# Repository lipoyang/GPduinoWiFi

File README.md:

GPduino WiFi
=========

## 概要
GPduino WiFiは、ESP8266搭載のWiFiラジコン制御ボードです。  
GPduinoに関する詳細は、[GPduinoサポートページ](http://lipoyang.net/gpduino)をごらんください。  
GPduinoWiFiの回路/基板設計データとプリセットファームウェアのソースをここに公開します。

## ファイル一覧

* firm/GPduinoWiFi/ : ファームウェア(ESP8266のArduinoスケッチ)
* hard/GPduinoWiFi/
	* GPduinoWiFi.sch/brd: 回路/基板設計データ(Eagle形式)
	* GPduinoWiFi.pdf: 回路図(PDF)
	* GPduinoWiFi_BOM.xlsx: BOMリスト(Excel形式)
	* GPduinoWiFi.GBL/GBO/GBP/GBS/GML/GTL/GTO/GTP/GTS/TXT: ガーバデータ
* LICENSE: Apache Licence 2.0です。
	* ただし、回路/基板設計は、Creative Commons Attribution Share-Alike 3.0です。
* README.md これ

## ファームウェアの書き込み
GPduino WiFi はESP8266を搭載しており、Arduinoでファームウェアを開発できます。

* 書き込みには、USBシリアル変換基板が必要です。CN11に接続してください。
	* SparkFun製 FTDI Basic Breakout - 3.3V を推奨します。かならず、3.3Vのものを使用してください。
* まず、ArduinoIDE をインストールしておきます。 (ここでは 1.6.9 を使用)
* [ファイル] > [環境設定] > [Additional Boards Manager URLs:]に下記URLをコピペ
	* http://arduino.esp8266.com/stable/package_esp8266com_index.json (安定版)
	* http://arduino.esp8266.com/staging/package_esp8266com_index.json (開発版)
* [ツール] > [ボード] > [ボードマネージャ] で [esp8266] をインストール
* [ツール] > [ボード] で [Generic ESP8266 Module]を選択
	* Flash Mode : QIO
	* Flash Frequency : 40MHz
	* Upload Using : Serial
	* CPU Frequency : 80MHz
	* Flash Size : 4M(3M SPIFFS)　(3MBをファイルシステムで使用 / 1MBをスケッチで使用)
	* Debug port : Disabled
	* Debug Level : None
	* Reset Method : nodemcu
	* Upload Speed : 115200
	* シリアルポート : USBシリアルのCOM番号
	* 書込装置 : USBasp
* BOOTボタン(SW3)を押し下げた状態で、RESETボタン(SW2)を押して離します。
* Uploadボタンで、ファームウェアを書き込みます。

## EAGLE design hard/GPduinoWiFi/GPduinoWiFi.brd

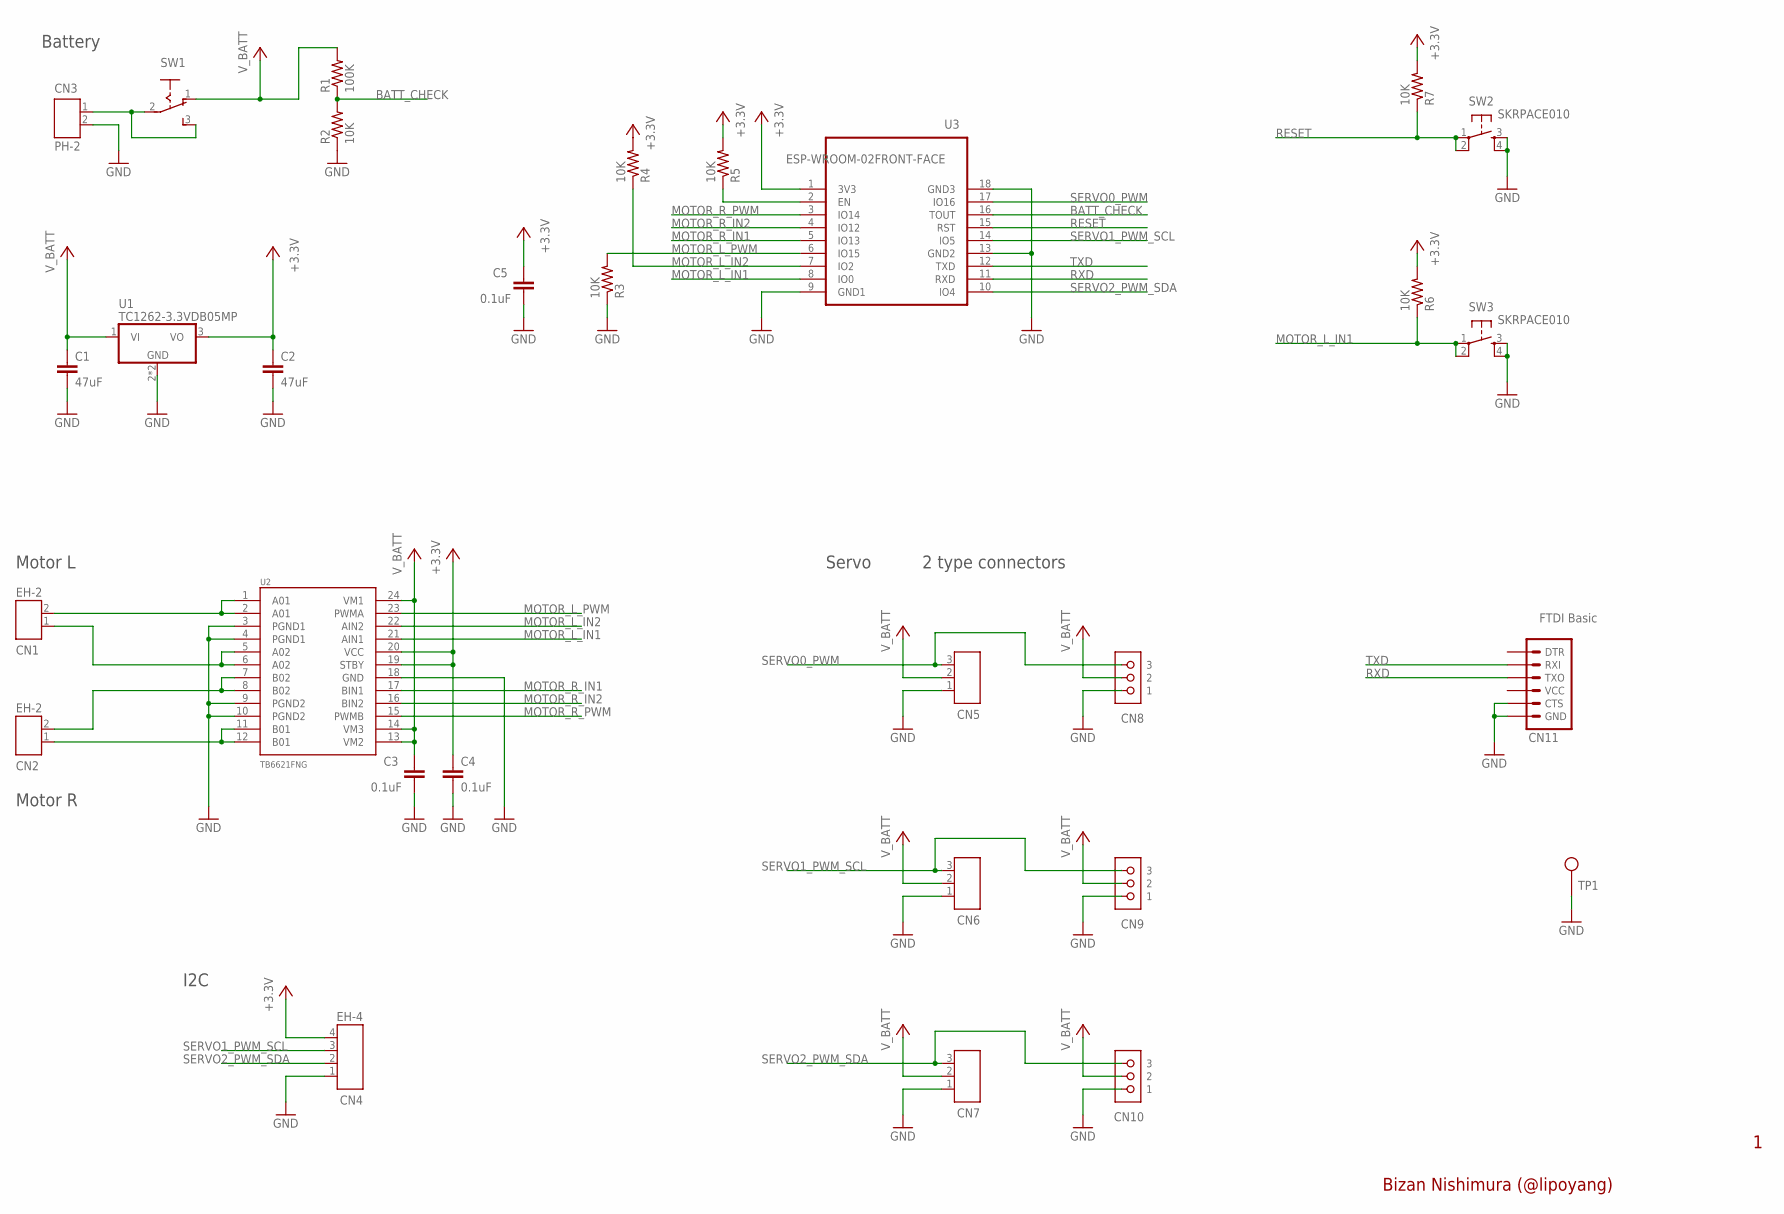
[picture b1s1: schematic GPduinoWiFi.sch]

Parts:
C1, C2: 47uF; C3216
C3, C4, C5: 0.1uF; C1608
CN1, CN2: EH-2
CN3: PH-2
CN4: EH-4
CN5, CN6, CN7: PICOBLADE-3
CN8, CN9, CN10: cn6; CON_RC_SERVO
CN11: FTDI Basic; 1X06
R1: 100K; 0603-RES
R2, R3, R4, R5, R6, R7: 10K; 0603-RES
SW1: SW1; SLIDE-SW
SW2, SW3: SKRPACE010
TP1: TEST_PIN
U1: TC1262-3.3VDB05MP; SOT223
U2: TB6621FNG; SSOP24
U3: ESP-WROOM-02FRONT-FACE; FRONT-FACE

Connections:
+3V3: C2.1, C4.1, C5.1, CN4.4, R4.2, R5.2, R6.2, R7.2, U1.3 (VO), U2.19 (STBY), U2.20 (VCC), U3.1 (3V3)
A01: CN1.2, U2.1 (A01), U2.2 (A01)
A02: CN1.1, U2.5 (A02), U2.6 (A02)
BATT_CHECK: R1.1, R2.2, U3.16 (TOUT)
GND: C1.2, C2.2, C3.2, C4.2, C5.2, CN3.2, CN4.1, CN5.1, CN6.1, CN7.1, CN8.1, CN9.1, CN10.1, CN11.5 (CTS), CN11.6 (GND), R2.1, R3.1, SW2.3, SW2.4, SW3.3, SW3.4, TP1.1, U1.2 (GND), U1.4 (GND), U2.3 (PGND1), U2.4 (PGND1), U2.9 (PGND2), U2.10 (PGND2), U2.18 (GND), U3.9 (GND1), U3.13 (GND2), U3.18 (GND3)
MOTOR_L_IN1: R6.1, SW3.1, SW3.2, U2.21 (AIN1), U3.8 (IO0)
MOTOR_L_IN2: R4.1, U2.22 (AIN2), U3.7 (IO2)
MOTOR_L_PWM: R3.2, U2.23 (PWMA), U3.6 (IO15)
MOTOR_R_IN1: U2.17 (BIN1), U3.5 (IO13)
MOTOR_R_IN2: U2.16 (BIN2), U3.4 (IO12)
MOTOR_R_PWM: U2.15 (PWMB), U3.3 (IO14)
unnamed: CN3.1, SW1.2, SW1.3 (S)
unnamed: R5.1, U3.2 (EN)
unnamed: CN2.1, U2.11 (B01), U2.12 (B01)
unnamed: CN2.2, U2.7 (B02), U2.8 (B02)
RESET: R7.1, SW2.1, SW2.2, U3.15 (RST)
RXD: CN11.3 (TXO), U3.11 (RXD)
SERVO0_PWM: CN5.3, CN8.3, U3.17 (IO16)
SERVO1_PWM_SCL: CN4.3, CN6.3, CN9.3, U3.14 (IO5)
SERVO2_PWM_SDA: CN4.2, CN7.3, CN10.3, U3.10 (IO4)
TXD: CN11.2 (RXI), U3.12 (TXD)
V_BATT: C1.1, C3.1, CN5.2, CN6.2, CN7.2, CN8.2, CN9.2, CN10.2, R1.2, SW1.1 (O), U1.1 (VI), U2.13 (VM2), U2.14 (VM3), U2.24 (VM1)

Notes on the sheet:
Battery
Servo
Motor L
Bizan Nishimura (@lipoyang)
2 type connectors
Motor R
I2C

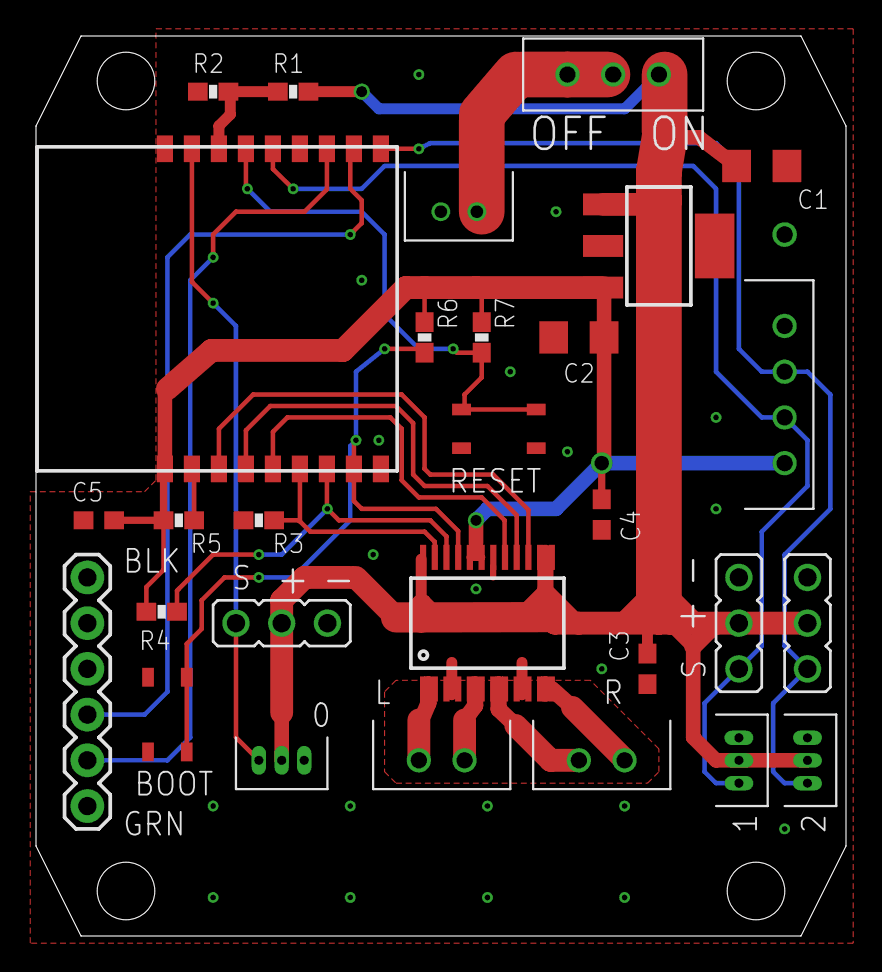
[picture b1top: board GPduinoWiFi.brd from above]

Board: 2 copper layers, 45.0 x 50.0 mm, 30 parts (0 on the bottom side), 22 nets.

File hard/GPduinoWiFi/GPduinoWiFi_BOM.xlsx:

GPduino WiFi BOM
基板本体キバンホンタイ
No | Reference | Part Number | Vender | Description | DNP | Qty | Unit Price | Price | Lot Size | Supplier | Supplier Code
1 | C1,2 | 47u(3216) | (generic) | 3216型ガタ |  | 2 | 30 | 60 | 10 | 秋月アキヅキ | P-06040
2 | C3,4,5 | 0.1u(1608) | (generic) | 1608型ガタ |  | 3 | 0.32500000000000001 | 0.97500000000000009 | 4000 | 秋月アキヅキ | P-01299
3 | CN1,2 | S2B-EH | JST | EH 2極 L型ポストキョクガタ | DNP | 0 | 16 | 0 | 1 | 共立キョウリツ | -
4 | CN3 | S2B-PH-K-S | JST | PH 2極 L型ポストキョクガタ |  | 1 | 16 | 16 | 1 | 共立キョウリツ | -
5 | CN4 | B4B-EH-A | JST | EH 4極 I型ポストキョクガタ | DNP | 0 | 21 | 0 | 1 | 共立キョウリツ | -
6 | CN5 | 53048-0310 | Molex | PicoBlade 3極 L型ポストキョクガタ | DNP (部品は付属)ブヒンフゾク | 1 | 45 | 45 | 5 | RS | 319-1092
7 | CN6,7 | 53047-0310 | Molex | PicoBlade 3極 I型ポストガタ | DNP | 0 | 29 | 0 | 5 | RS | 319-1064
8 | CN8 | - | (generic) | ピンヘッダ 3ピン | DNP (部品は付属)ブヒンフゾク | 1 | 35 | 35 | 16 | 共立キョウリツ | -
9 | CN9,10 | - | (generic) | ピンヘッダ 3ピン | DNP | 0 | 17 | 0 | 12 | 共立キョウリツ | -
10 | CN11 | 0 | (generic) | ピンヘッダ 6ピン I型ガタ | DNP (部品は付属)ブヒンフゾク | 1 | 70 | 70 | 8 | 共立キョウリツ | -
12 | R1 | 100k(1608) | (generic) | 1608型 |  | 1 | 0.2 | 0.2 | 2500 | 秋月アキヅキ | R-06104
13 | R2,3,4,5,6,7 | 10k(1608) | (generic) | 1608型 |  | 6 | 0.2 | 1.2000000000000002 | 2500 | 秋月アキヅキ | R-06103
14 | SW1 | SS-12SDP2 | NKK | スライドスイッチ | DNP (部品は付属)ブヒンフゾク | 1 | 66 | 66 | 1 | 共立キョウリツ | 391139
15 | SW2,3 | SKRPACE010 | ALPS | 表面実装タクトスイッチヒョウメンジッソウ |  | 2 | 20 | 40 | 5 | 秋月アキヅキ | P-06185
16 | U1 | TC1262-3.3VDB05MP | Microchip | LDO, 3.3V-0.5A, SOT-223型ガタ |  | 1 | 81 | 81 | 1 | RS | 703-7905
17 | U2 | TB6621FNG | Toshiba | Dual DCモータドライバ |  | 1 | 306 | 306 | 1 | RS | 770-3797
18 | U3 | ESP-WROOM-02 | Espressif Systems | ESP8266 WiFiモジュール |  | 1 | 550 | 550 | 1 | 秋月アキヅキ | M-09607
19 | - | - | Elecrow | 基板キバン |  | 1 | 275.10000000000002 | 275.10000000000002 | 10 | Elecrow | -
20 | - | PH2P300L | Marutsu | PH 2極 アッセンブルケーブルキョク |  | 1 | 54 | 54 | 1 | マルツ | -
 |  |  |  |  |  |  | Total | 1600.4749999999999

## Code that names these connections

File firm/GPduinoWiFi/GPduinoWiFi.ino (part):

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void udpComm_callback(char* buff);

// ピン番号 (デジタル)
#define MOTOR_R_PWM    14
#define MOTOR_R_IN2    12
#define MOTOR_R_IN1    13
#define MOTOR_L_PWM    15
#define MOTOR_L_IN2    2
#define MOTOR_L_IN1    0
#define SERVO0_PWM     16
#define SERVO1_PWM     5
#define SERVO2_PWM     4

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    digitalWrite(MOTOR_L_IN2, LOW);
    digitalWrite(MOTOR_R_IN1, LOW);
    digitalWrite(MOTOR_R_IN2, LOW);
    pinMode(MOTOR_L_IN1, OUTPUT);
    pinMode(MOTOR_L_IN2, OUTPUT);
    pinMode(MOTOR_R_IN1, OUTPUT);
    pinMode(MOTOR_R_IN2, OUTPUT);
    
    // モード判定
    //int mode_check = analogRead( MODE_CHECK );
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 */
void ctrl_motor(int ch, int val)
{
    static const int IN1[]={MOTOR_L_IN1, MOTOR_R_IN1};
    static const int IN2[]={MOTOR_L_IN2, MOTOR_R_IN2};
    static const int PWM[]={MOTOR_L_PWM, MOTOR_R_PWM};
    
    int l,r;
    int lpwm,rpwm,lin1,lin2,rin1,rin2;
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
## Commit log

2016-10-21 ・ファームウェアのソースを追加
2016-10-21 ・基板のCADデータを追加
2016-10-23 ・回路図の修正（リビジョン番号のみ）
2016-10-23 ・READMEの記述
2016-10-27 ・車両モード設定機能の追加
2016-10-27 ・READMEの修正
2016-11-21 ・モータ出力のバグ修正

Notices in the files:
parts and their libraries:
lipoyang_frame: Released under the Creative Commons
Attribution Share-Alike 3.0 License
http://creativecommons.org/licenses/by-sa/3.0
